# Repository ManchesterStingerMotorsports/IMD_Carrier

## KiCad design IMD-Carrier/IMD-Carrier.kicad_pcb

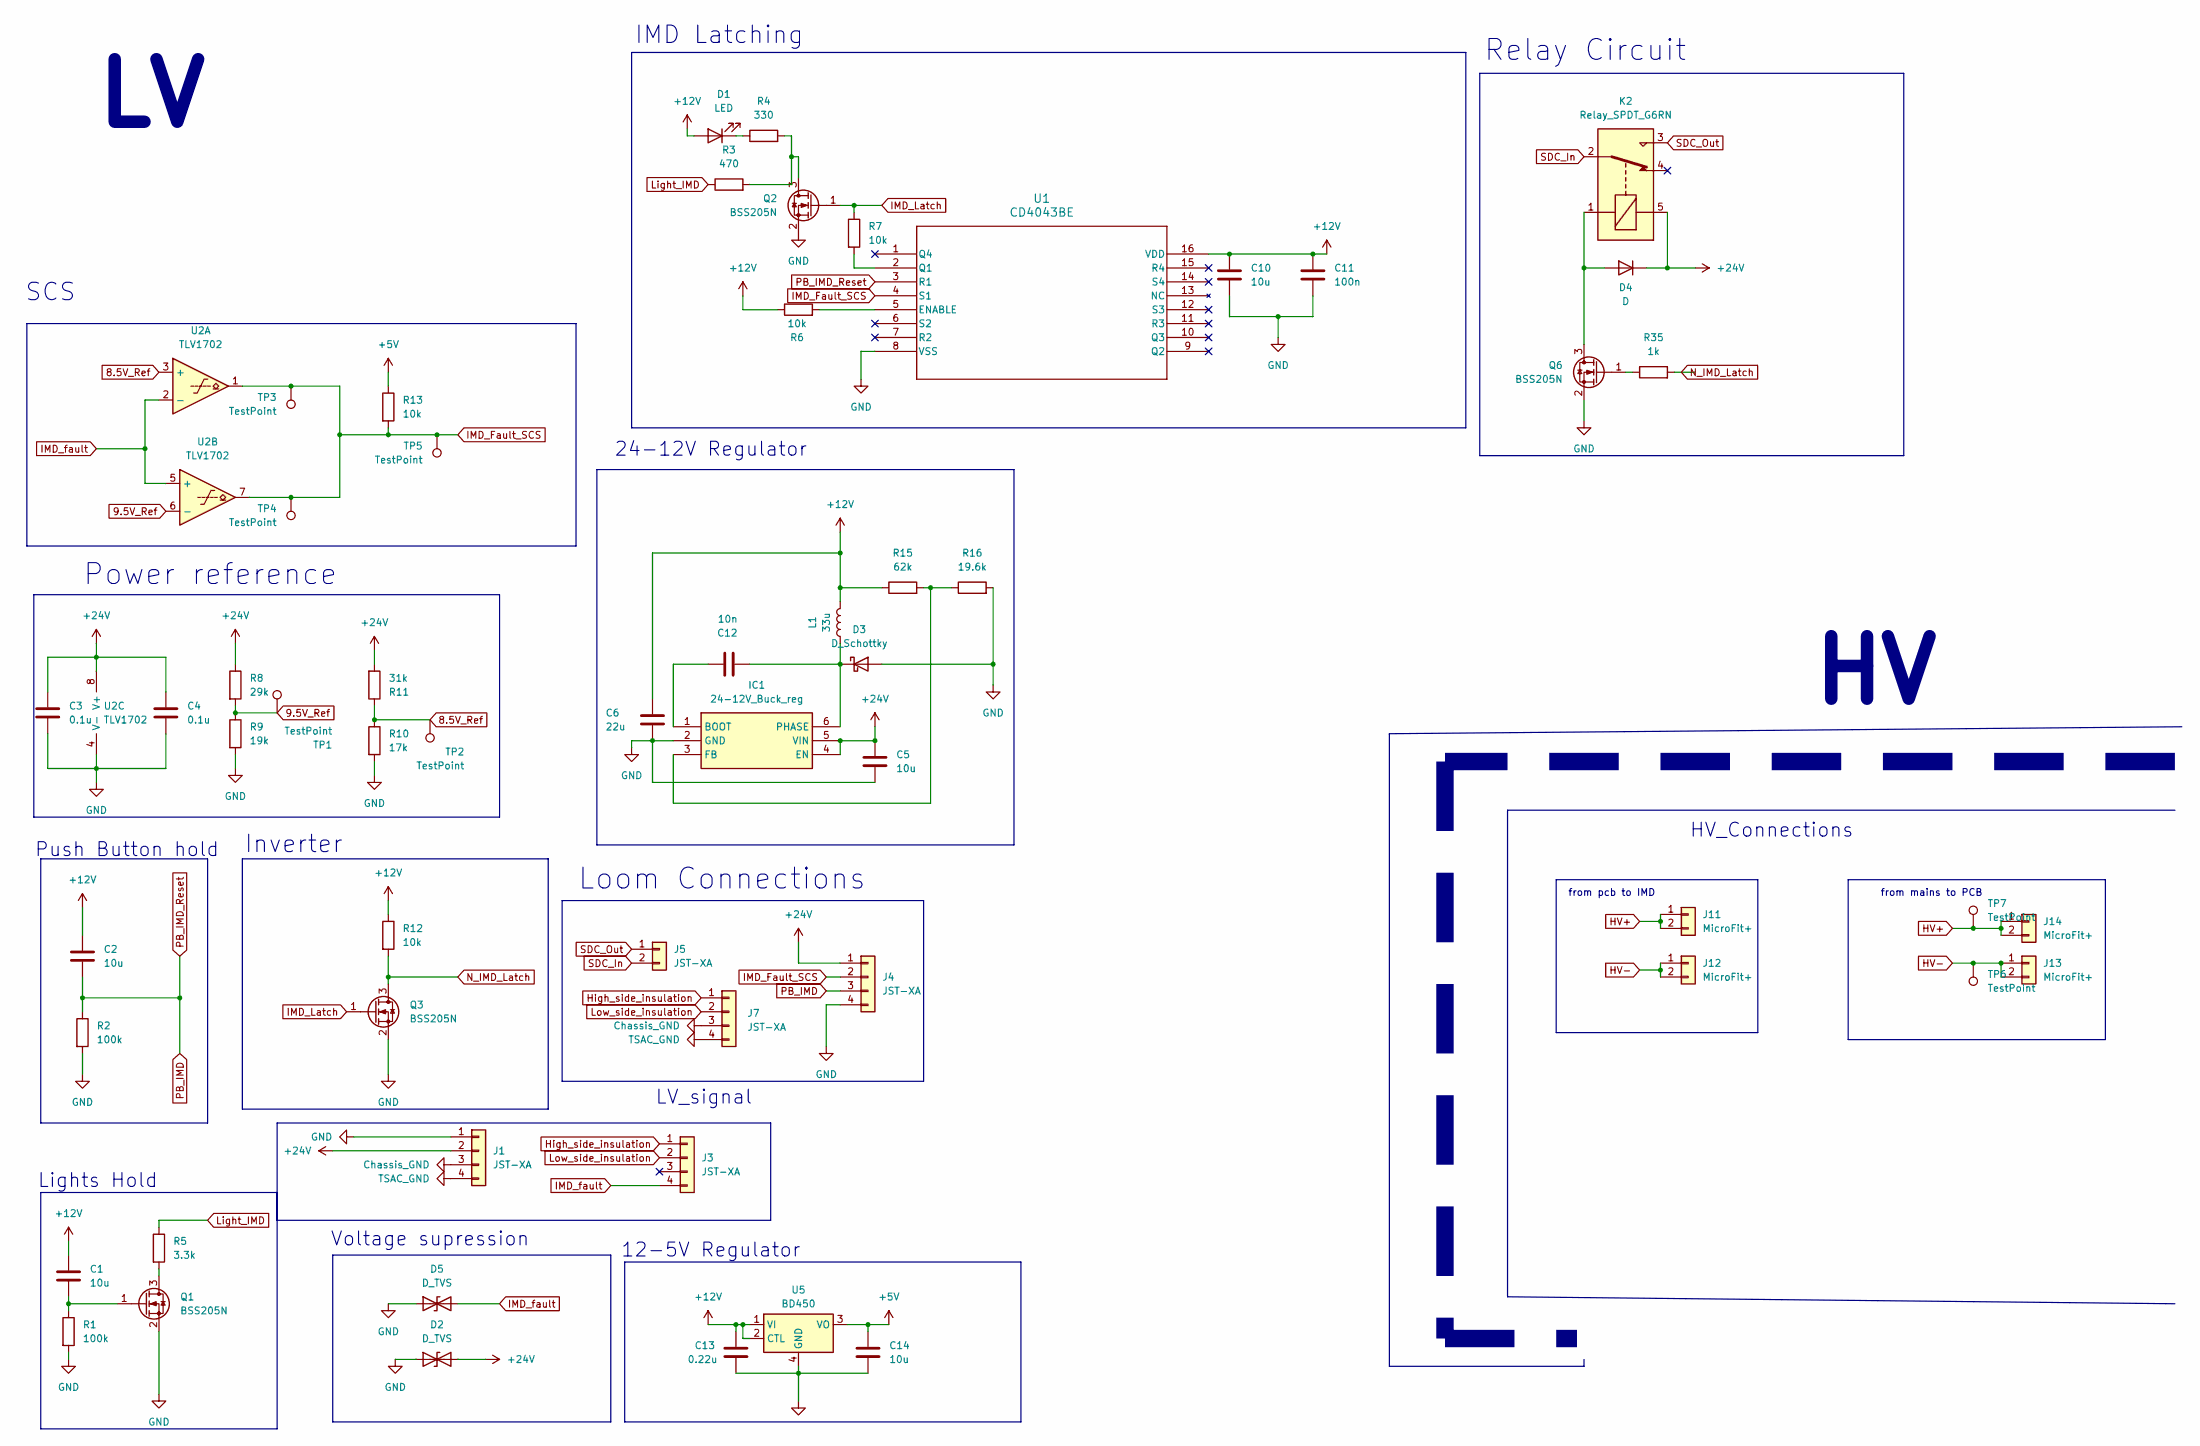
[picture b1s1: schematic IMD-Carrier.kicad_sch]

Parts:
C1, C2, C5, C10: 10u; C_0805_2012Metric
C3, C4: 0.1u; C_0805_2012Metric
C6: 22u; C_0805_2012Metric
C11: 100n; C_0805_2012Metric
C12: 10n; C_0805_2012Metric
C13: 0.22u; C_0805_2012Metric; Part number 7235051
C14: 10u; C_0805_2012Metric; Part number 2478051
D1: LED; LED_0805_2012Metric
D2, D5: D_TVS; D_0805_2012Metric
D3: D_Schottky; D_0805_2012Metric
D4: D; D_0805_2012Metric
IC1: 24-12V_Buck_reg; SOT94P279X130-6N; Manufacturer_Part_Number RT8259GE
J1, J3, J4, J7: JST-XA; Connector_JST-XA_4POS
J5: JST-XA; Connector_JST-XA_2POS
J11, J12, J13, J14: MicroFit+; Connector_MicroFit-Plus_2POS
K2: Relay_SPDT_G6RN
L1: 33u; L_0805_2012Metric
Q1, Q2, Q3, Q6: BSS205N; MOSFET_Single_SOT-23
R1, R2: 100k; R_0805_2012Metric
R3: 470; R_0805_2012Metric
R4: 330; R_0805_2012Metric
R5: 3.3k; R_0805_2012Metric
R6, R7, R12, R13: 10k; R_0805_2012Metric
R8: 29k; R_0805_2012Metric
R9: 19k; R_0805_2012Metric
R10: 17k; R_0805_2012Metric
R11: 31k; R_0805_2012Metric
R15: 62k; R_0805_2012Metric
R16: 19.6k; R_0805_2012Metric
R35: 1k; R_0805_2012Metric
TP1, TP2, TP3, TP4, TP5, TP6, TP7: TestPoint; TestPoint_Pad_1.0x1.0mm
U1: CD4043BE; SOP127P780X200-16N
U2: TLV1702; Comparator_Dual_VSSOP-8
U5: BD450; Regulator_Linear_SOT-223-4; Part Number 2 BD450M2WFP3-CE2CT-ND

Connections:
8.5V_Ref: R10.1, R11.1, TP2.1 (1_1), U2.3 (+)
9.5V_Ref: R8.2, R9.1, TP1.1 (1_1), U2.6 (-)
+5V: C14.1, R13.1, U5.3 (VO)
+12V: C1.1, C2.1, C6.1, C10.1, C11.1, C13.1, D1.2 (A), L1.2, R6.1, R12.1, R15.1, U1.16 (VDD), U5.1 (VI), U5.2 (CTL)
+24V: C3.1, C4.1, C5.1, D2.2 (A2), D4.1 (K), IC1.4 (EN), IC1.5 (VIN), J1.2, J4.1, K2.5, R8.1, R11.2, U2.8 (V+)
Chassis_GND: J1.3, J7.3
GND: C3.2, C4.2, C5.2, C6.2, C10.2, C11.2, C13.2, C14.2, D2.1 (A1), D3.2 (A), D5.1 (A1), IC1.2 (GND), J1.1, J4.4, Q1.2 (S), Q2.2 (S), Q3.2 (S), Q6.2 (S), R1.2, R2.2, R9.2, R10.2, R16.2, U1.8 (VSS), U2.4 (V-), U5.4 (GND)
HV+: J11.1, J11.2, J14.1, J14.2, TP7.1 (1_1)
HV-: J12.1, J12.2, J13.1, J13.2, TP6.1 (1_1)
High_side_insulation: J3.1, J7.1
IMD_Fault_SCS: J4.2, R13.2, TP3.1 (1_1), TP4.1 (1_1), TP5.1 (1_1), U1.4 (S1), U2.1, U2.7
IMD_Latch: Q2.1 (G), Q3.1 (G), R7.1
IMD_fault: D5.2 (A2), J3.4, U2.2 (-), U2.5 (+)
Light_IMD: R3.1, R5.1
Low_side_insulation: J3.2, J7.2
N_IMD_Latch: Q3.3 (D), R12.2, R35.2
unnamed: D1.1 (K), R4.1
unnamed: C12.1, D3.1 (K), IC1.6 (PHASE), L1.1
unnamed: D4.2 (A), K2.1, Q6.3 (D)
unnamed: C12.2, IC1.1 (BOOT)
unnamed: IC1.3 (FB), R15.2, R16.1
unnamed: Q1.3 (D), R5.2
unnamed: C1.2, Q1.1 (G), R1.1
unnamed: Q2.3 (D), R3.2, R4.2
unnamed: Q6.1 (G), R35.1
unnamed: R6.2, U1.5 (ENABLE)
unnamed: R7.2, U1.2 (Q1)
PB_IMD: C2.2, J4.3, R2.1, U1.3 (R1)
SDC_In: J5.2, K2.2
SDC_Out: J5.1, K2.3
TSAC_GND: J1.4, J7.4

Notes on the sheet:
Inverter
Power reference
Lights Hold
24-12V Regulator
SCS
Loom Connections
from mains to PCB
12-5V Regulator
LV_signal
HV_Connections
IMD Latching
from pcb to IMD
Push Button hold
Voltage supression
Relay Circuit

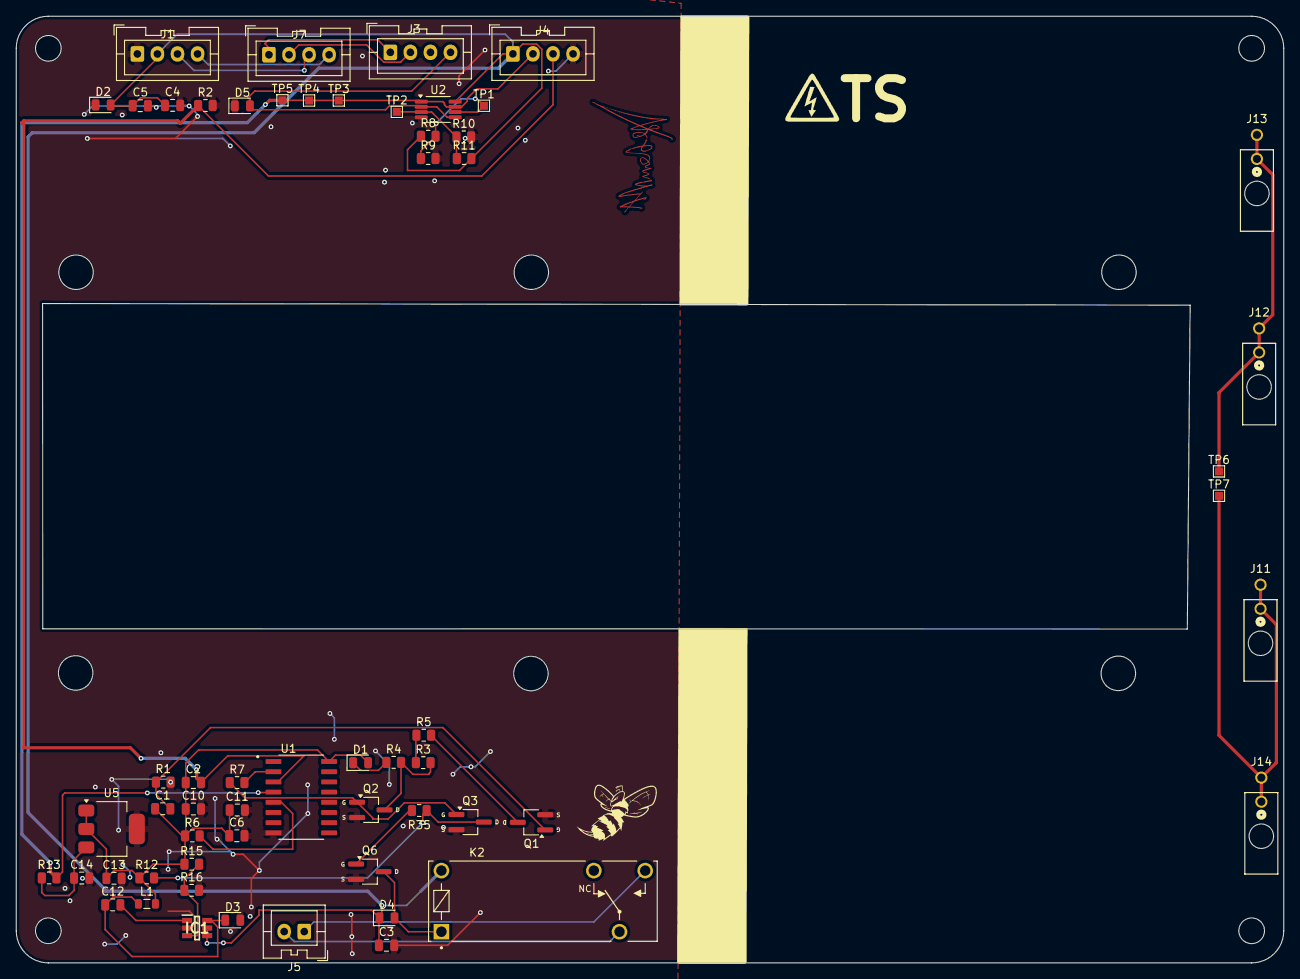
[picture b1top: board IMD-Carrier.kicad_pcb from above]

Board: 2 copper layers, 158.0 x 118.0 mm, 58 parts (0 on the bottom side), 31 nets.

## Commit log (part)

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2026-03-23 Intial schematic for the IMD carrier
2026-03-24 Fully finished schematic+partial routing
    -Removed the need for regulators by changing all logic to 12V
    -Current Calculations for power connections still need to be done
2026-03-25 finished the routing of the PCB (to be checked)
2026-04-10 Finished PCB routing (not final)
2026-04-11 FInished routing
